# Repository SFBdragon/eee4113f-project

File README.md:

# EEE4113F Project - Antarctic Measurement System Communication Module

_Group 5_

---

TODO

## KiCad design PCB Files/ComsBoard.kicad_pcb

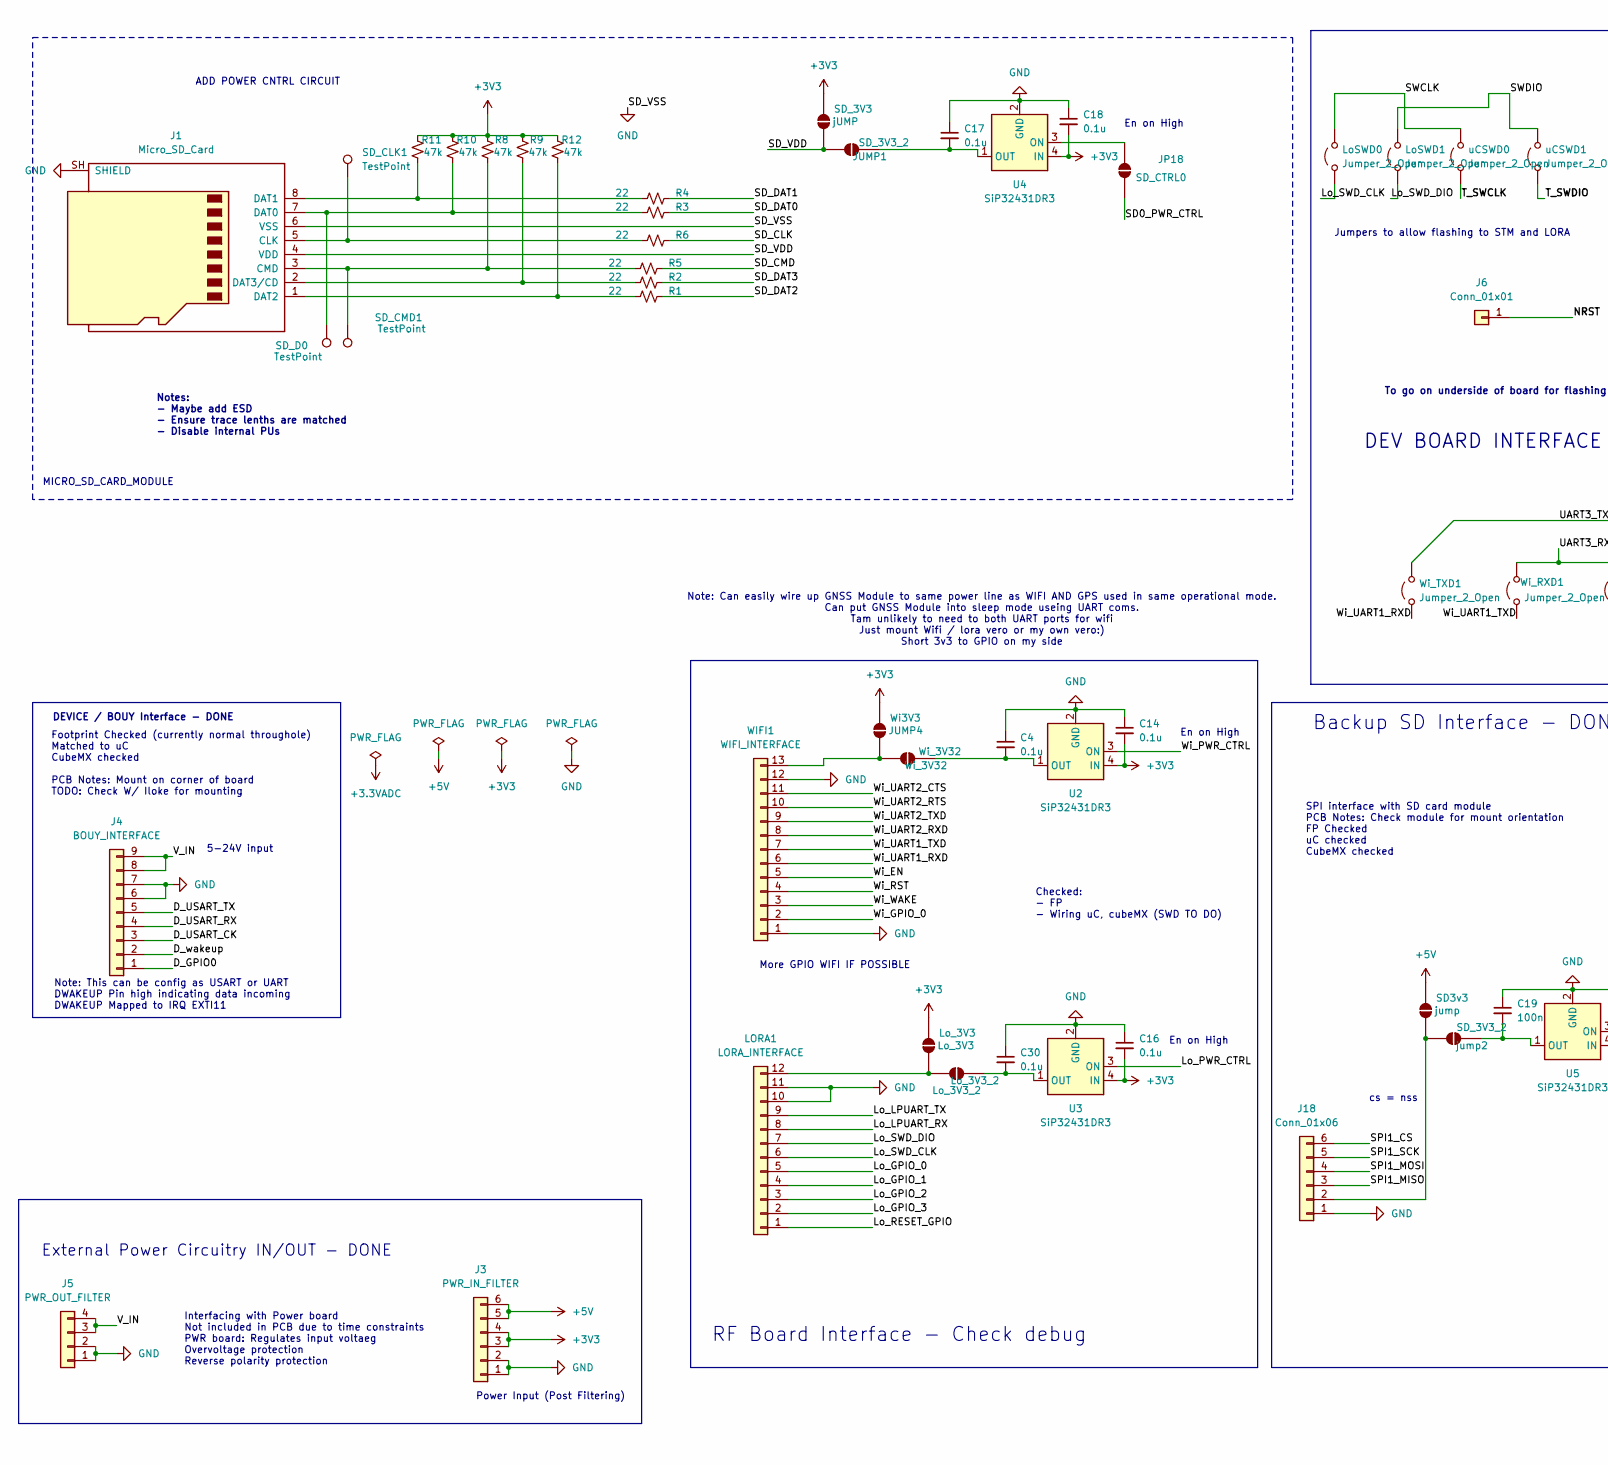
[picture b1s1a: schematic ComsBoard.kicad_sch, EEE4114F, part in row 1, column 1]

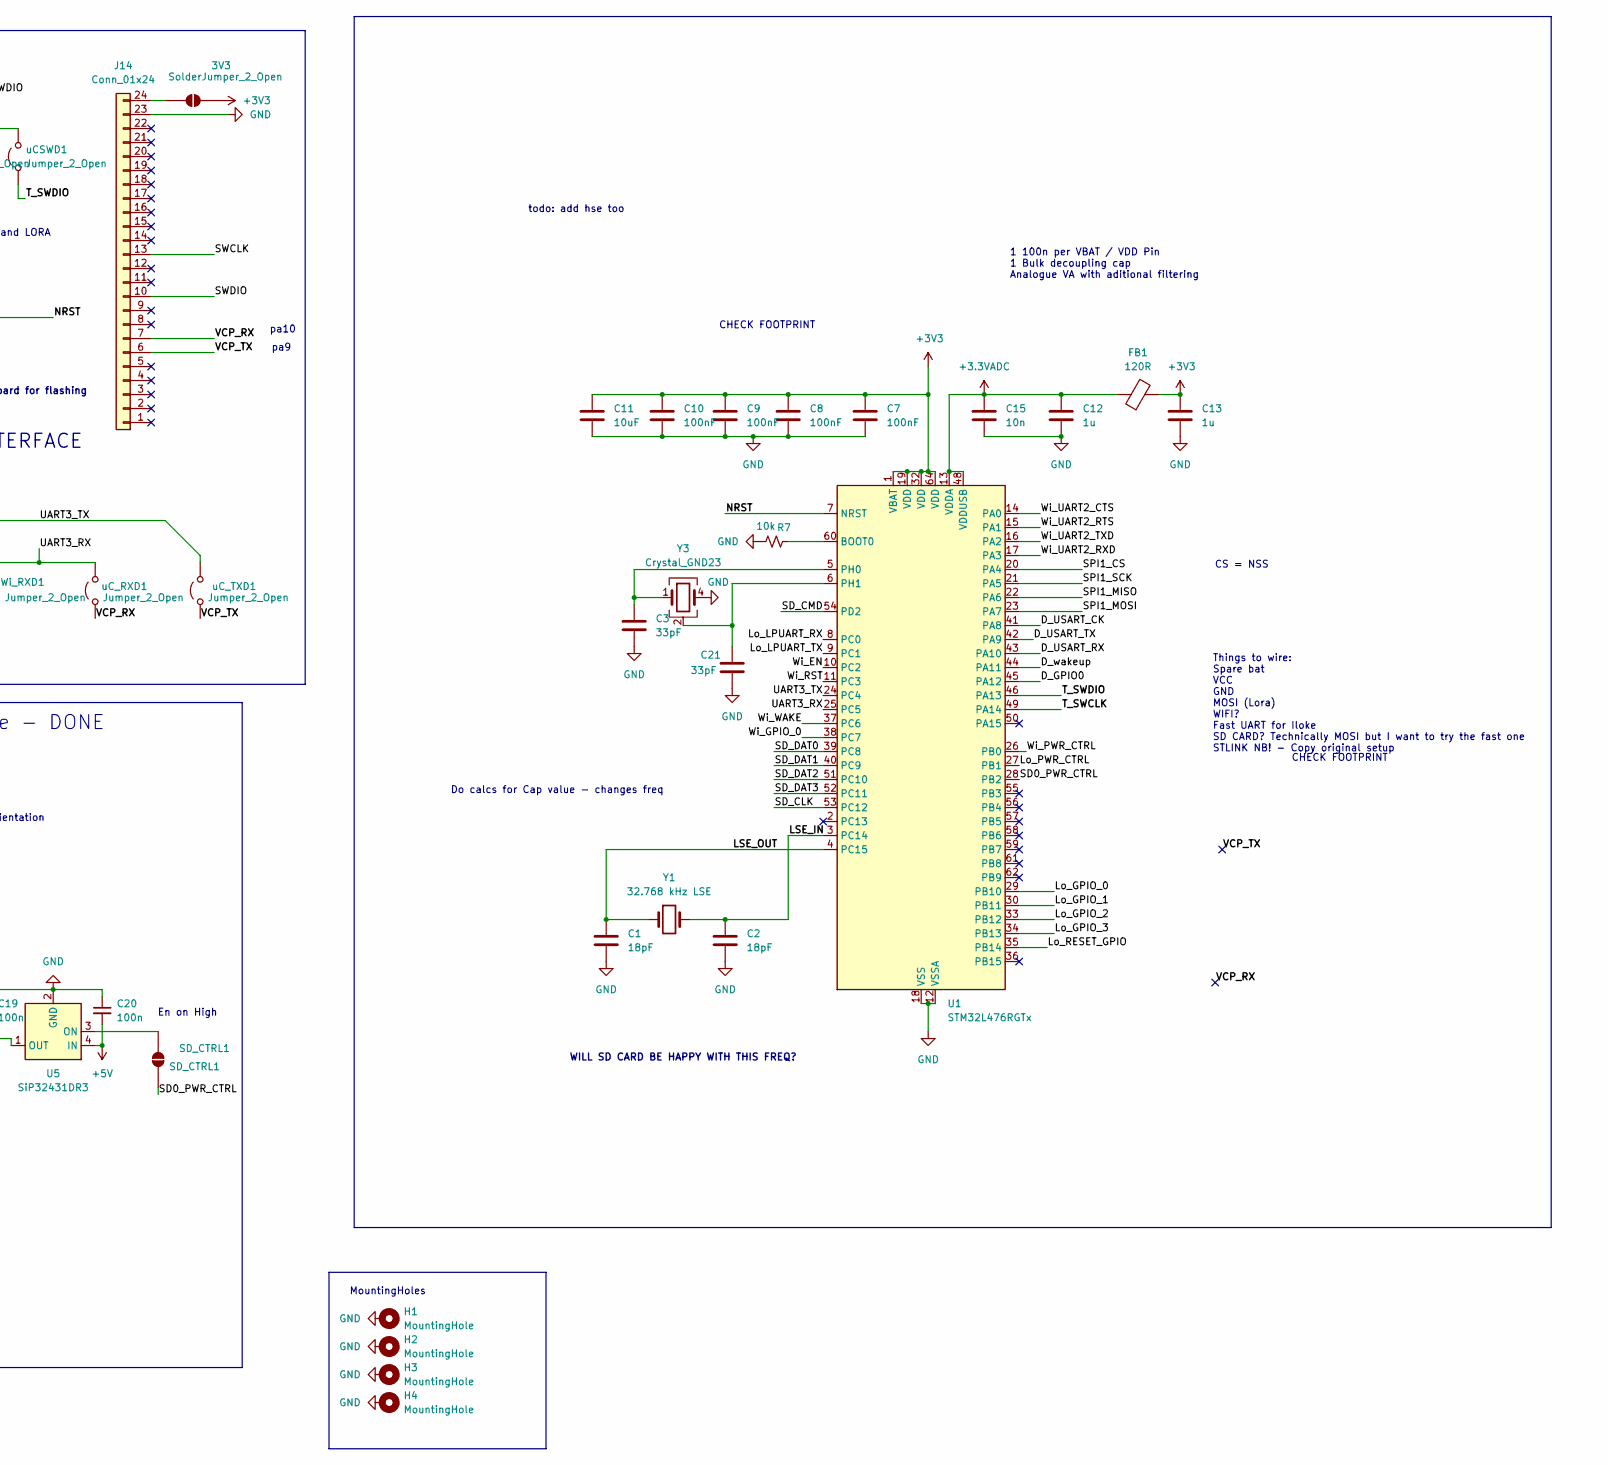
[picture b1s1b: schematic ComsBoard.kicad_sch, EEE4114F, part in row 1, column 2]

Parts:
3V3: SolderJumper_2_Open; SolderJumper-2_P1.3mm_Open_RoundedPad1.0x1.5mm
C1, C2: 18pF; C_0603_1608Metric
C3, C21: 33pF; C_0603_1608Metric
C4, C14, C16, C17, C18, C30: 0.1u; C_0603_1608Metric
C7, C8, C9, C10: 100nF; C_0603_1608Metric
C11: 10uF; C_0603_1608Metric
C12, C13: 1u; C_0603_1608Metric
C15: 10n; C_0603_1608Metric
C19, C20: 100n; C_0603_1608Metric
FB1: 120R; L_0603_1608Metric
H1, H2, H3, H4: MountingHole; MountingHole_3.2mm_M3_DIN965_Pad
J1: Micro_SD_Card; microSD_HC_Molex_47219-2001
J3: PWR_IN_FILTER; PinHeader_1x06_P2.54mm_Vertical
J4: BOUY_INTERFACE; PinHeader_1x09_P2.54mm_Vertical
J5: PWR_OUT_FILTER; PinHeader_1x04_P2.54mm_Vertical
J6: Conn_01x01; PinSocket_1x01_P2.54mm_Vertical
J14: Conn_01x24; PinSocket_1x24_P2.54mm_Vertical
J18: Conn_01x06; PinHeader_1x06_P2.54mm_Vertical
JP18: SD_CTRL0; SolderJumper-2_P1.3mm_Open_RoundedPad1.0x1.5mm
JUMP1: SD_3V3_2; SolderJumper-2_P1.3mm_Open_RoundedPad1.0x1.5mm
LORA1: LORA_INTERFACE; PinHeader_1x12_P2.54mm_Vertical
LoSWD0, LoSWD1: Jumper_2_Open; PinSocket_1x02_P2.54mm_Vertical
Lo_3V3: Lo_3V3; SolderJumper-2_P1.3mm_Open_RoundedPad1.0x1.5mm
Lo_3V3_2: Lo_3V3_2; SolderJumper-2_P1.3mm_Open_RoundedPad1.0x1.5mm
R1, R2, R3, R4, R5, R6: 22; R_0603_1608Metric
R7: 10k; R_0603_1608Metric
R8, R9, R10, R11, R12: 47k; R_0603_1608Metric
SD3v3: jump; SolderJumper-2_P1.3mm_Open_RoundedPad1.0x1.5mm
SD_3V3: jUMP; SolderJumper-2_P1.3mm_Open_RoundedPad1.0x1.5mm
SD_CLK1: TestPoint; TestPoint_Pad_D1.5mm
SD_CMD1: TestPoint; TestPoint_Pad_D1.5mm
SD_CTRL1: SD_CTRL1; SolderJumper-2_P1.3mm_Open_RoundedPad1.0x1.5mm
SD_D0: TestPoint; TestPoint_Pad_D1.5mm
U1: STM32L476RGTx; LQFP-64_10x10mm_P0.5mm
U2, U3, U4, U5: SiP32431DR3; SOT-363_SC-70-6
WIFI1: WIFI_INTERFACE; PinSocket_1x13_P2.54mm_Vertical
Wi3V3: JUMP4; SolderJumper-2_P1.3mm_Open_RoundedPad1.0x1.5mm
Wi_3V32: Wi_3V32; SolderJumper-2_P1.3mm_Open_RoundedPad1.0x1.5mm
Wi_RXD1: Jumper_2_Open; PinSocket_1x02_P2.54mm_Vertical
Wi_TXD1: Jumper_2_Open; PinSocket_1x02_P2.54mm_Vertical
Y1: 32.768 kHz LSE; Crystal_SMD_3215-2Pin_3.2x1.5mm
Y3: Crystal_GND23; Crystal_SMD_3225-4Pin_3.2x2.5mm
jump2: SD_3V3_2; SolderJumper-2_P1.3mm_Open_RoundedPad1.0x1.5mm
uCSWD0, uCSWD1: Jumper_2_Open; PinSocket_1x02_P2.54mm_Vertical
uC_RXD1: Jumper_2_Open; PinSocket_1x02_P2.54mm_Vertical
uC_TXD1: Jumper_2_Open; PinSocket_1x02_P2.54mm_Vertical

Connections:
+3.3VADC: C12.1, C15.1, FB1.1, U1.13 (VDDA), U1.48 (VDDUSB)
+5V: C20.2, J3.5, J3.6, SD3v3.2 (B), U5.4 (IN)
/D_GPIO0: J4.1, U1.45 (PA12)
/D_USART_CK: J4.3, U1.41 (PA8)
/D_USART_RX: J4.4, U1.43 (PA10)
/D_USART_TX: J4.5, U1.42 (PA9)
/D_wakeup: J4.2, U1.44 (PA11)
/LSE_IN: C2.1, U1.3 (PC14), Y1.2
/LSE_OUT: C1.1, U1.4 (PC15), Y1.1
/Lo_GPIO_0: LORA1.5, U1.29 (PB10)
/Lo_GPIO_1: LORA1.4, U1.30 (PB11)
/Lo_GPIO_2: LORA1.3, U1.33 (PB12)
/Lo_GPIO_3: LORA1.2, U1.34 (PB13)
/Lo_LPUART_RX: LORA1.8, U1.8 (PC0)
/Lo_LPUART_TX: LORA1.9, U1.9 (PC1)
/Lo_PWR_CTRL: U1.27 (PB1), U3.3 (ON)
/Lo_RESET_GPIO: LORA1.1, U1.35 (PB14)
/Lo_SWD_CLK: LORA1.6, LoSWD0.1 (A)
/Lo_SWD_DIO: LORA1.7, LoSWD1.1 (A)
/NRST: J6.1 (Pin_1_1), U1.7 (NRST)
/SD0_PWR_CTRL: JP18.2 (B), SD_CTRL1.2 (B), U1.28 (PB2)
/SD_CLK: R6.2, U1.53 (PC12)
/SD_CMD: R5.2, U1.54 (PD2)
/SD_DAT0: R3.2, U1.39 (PC8)
/SD_DAT1: R4.2, U1.40 (PC9)
/SD_DAT2: R1.2, U1.51 (PC10)
/SD_DAT3: R2.2, U1.52 (PC11)
/SPI1_CS: J18.6, U1.20 (PA4)
/SPI1_MISO: J18.3, U1.22 (PA6)
/SPI1_MOSI: J18.4, U1.23 (PA7)
/SPI1_SCK: J18.5, U1.21 (PA5)
/SWCLK: J14.13, LoSWD0.2 (B), uCSWD0.2 (B)
/SWDIO: J14.10, LoSWD1.2 (B), uCSWD1.2 (B)
/T_SWCLK: U1.49 (PA14), uCSWD0.1 (A)
/T_SWDIO: U1.46 (PA13), uCSWD1.1 (A)
/UART3_RX: U1.25 (PC5), Wi_RXD1.2 (B), uC_RXD1.2 (B)
/UART3_TX: U1.24 (PC4), Wi_TXD1.2 (B), uC_TXD1.2 (B)
/VCP_RX: J14.7, uC_RXD1.1 (A)
/VCP_TX: J14.6, uC_TXD1.1 (A)
/V_IN: J4.8, J4.9, J5.3, J5.4
/Wi_EN: U1.10 (PC2), WIFI1.5
/Wi_GPIO_0: U1.38 (PC7), WIFI1.2
/Wi_PWR_CTRL: U1.26 (PB0), U2.3 (ON)
/Wi_RST: U1.11 (PC3), WIFI1.4
/Wi_UART1_RXD: WIFI1.6, Wi_TXD1.1 (A)
/Wi_UART1_TXD: WIFI1.7, Wi_RXD1.1 (A)
/Wi_UART2_CTS: U1.14 (PA0), WIFI1.11
/Wi_UART2_RTS: U1.15 (PA1), WIFI1.10
/Wi_UART2_RXD: U1.17 (PA3), WIFI1.8
/Wi_UART2_TXD: U1.16 (PA2), WIFI1.9
/Wi_WAKE: U1.37 (PC6), WIFI1.3
GND: C1.2, C2.2, C3.2, C4.1, C7.2, C8.2, C9.2, C10.2, C11.2, C12.2, C13.2, C14.1, C15.2, C16.1, C17.1, C18.1, C19.1, C20.1, C21.2, C30.1, J1.6 (VSS), J1.SH (SHIELD), J3.1, J3.2, J4.6, J4.7, J5.1, J5.2, J14.23, J18.1, LORA1.10, LORA1.11, R7.1, U1.12 (VSSA), U1.18 (VSS), U1.31 (VSS), U1.47 (VSS), U1.63 (VSS), U2.2 (GND), U2.5 (GND), U3.2 (GND), U3.5 (GND), U4.2 (GND), U4.5 (GND), U5.2 (GND), U5.5 (GND), WIFI1.1, WIFI1.12, Y3.4; also elsewhere on the board
unnamed: 3V3.1 (A), J14.24
unnamed: J1.5 (CLK), R6.1, SD_CLK1.1 (1_1)
unnamed: J1.3 (CMD), R5.1, R8.1, SD_CMD1.1 (1_1)
unnamed: J1.7 (DAT0), R3.1, R10.1, SD_D0.1 (1_1)
unnamed: J1.8 (DAT1), R4.1, R11.1
unnamed: J1.1 (DAT2), R1.1, R12.1
unnamed: J1.2 (DAT3/CD), R2.1, R9.1
unnamed: J18.2, SD3v3.1 (A), jump2.2 (B)
unnamed: JP18.1 (A), U4.3 (ON)
unnamed: C17.2, JUMP1.1 (A), U4.1 (OUT)
unnamed: LORA1.12, Lo_3V3.1 (A), Lo_3V3_2.2 (B)
unnamed: C30.2, Lo_3V3_2.1 (A), U3.1 (OUT)
unnamed: SD_CTRL1.1 (A), U5.3 (ON)
unnamed: R7.2, U1.60 (BOOT0)
unnamed: C3.1, U1.5 (PH0), Y3.1
unnamed: C21.1, U1.6 (PH1), Y3.2 (G), Y3.3 (G)
unnamed: C4.2, U2.1 (OUT), Wi_3V32.1 (A)
unnamed: C19.2, U5.1 (OUT), jump2.1 (A)
unnamed: WIFI1.13, Wi3V3.1 (A), Wi_3V32.2 (B)

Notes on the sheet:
Note: Can easily wire up GNSS Module to same power line as WIFI AND GPS used in same operational mode. Can put GNSS Module into sleep mode useing UART coms. Tam unlikely to need to both UART ports for wifi Just mount Wifi / lora vero or my own vero:) Short 3v3 to GPIO on my side
More GPIO WIFI IF POSSIBLE
CHECK FOOTPRINT
cs = nss
SPI interface with SD card module PCB Notes: Check module for mount orientation FP Checked uC checked CubeMX checked
Footprint Checked (currently normal throughole) Matched to uC CubeMX checked PCB Notes: Mount on corner of board TODO: Check W/ Iloke for mounting
En on High
RF Board Interface - Check debug
Note: This can be config as USART or UART DWAKEUP Pin high indicating data incoming DWAKEUP Mapped to IRQ EXTI11
Things to wire: Spare bat VCC GND MOSI (Lora) WIFI? Fast UART for Iloke SD CARD? Technically MOSI but I want to try the fast one STLINK NB! - Copy original setup
DEVICE / BOUY Interface - DONE
WILL SD CARD BE HAPPY WITH THIS FREQ?
pa9
Power Input (Post Filtering)
CS = NSS
Interfacing with Power board Not included in PCB due to time constraints PWR board: Regulates input voltaeg Overvoltage protection Reverse polarity protection
External Power Circuitry IN/OUT - DONE
Notes: - Maybe add ESD - Ensure trace lenths are matched - Disable internal PUs
todo: add hse too
To go on underside of board for flashing
Jumpers to allow flashing to STM and LORA
pa10
Checked: - FP - Wiring uC, cubeMX (SWD TO DO)
Backup SD Interface - DONE
DEV BOARD INTERFACE
ADD POWER CNTRL CIRCUIT
MICRO_SD_CARD_MODULE
1 100n per VBAT / VDD Pin 1 Bulk decoupling cap Analogue VA with aditional filtering
5-24V input
MountingHoles
Do calcs for Cap value - changes freq

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
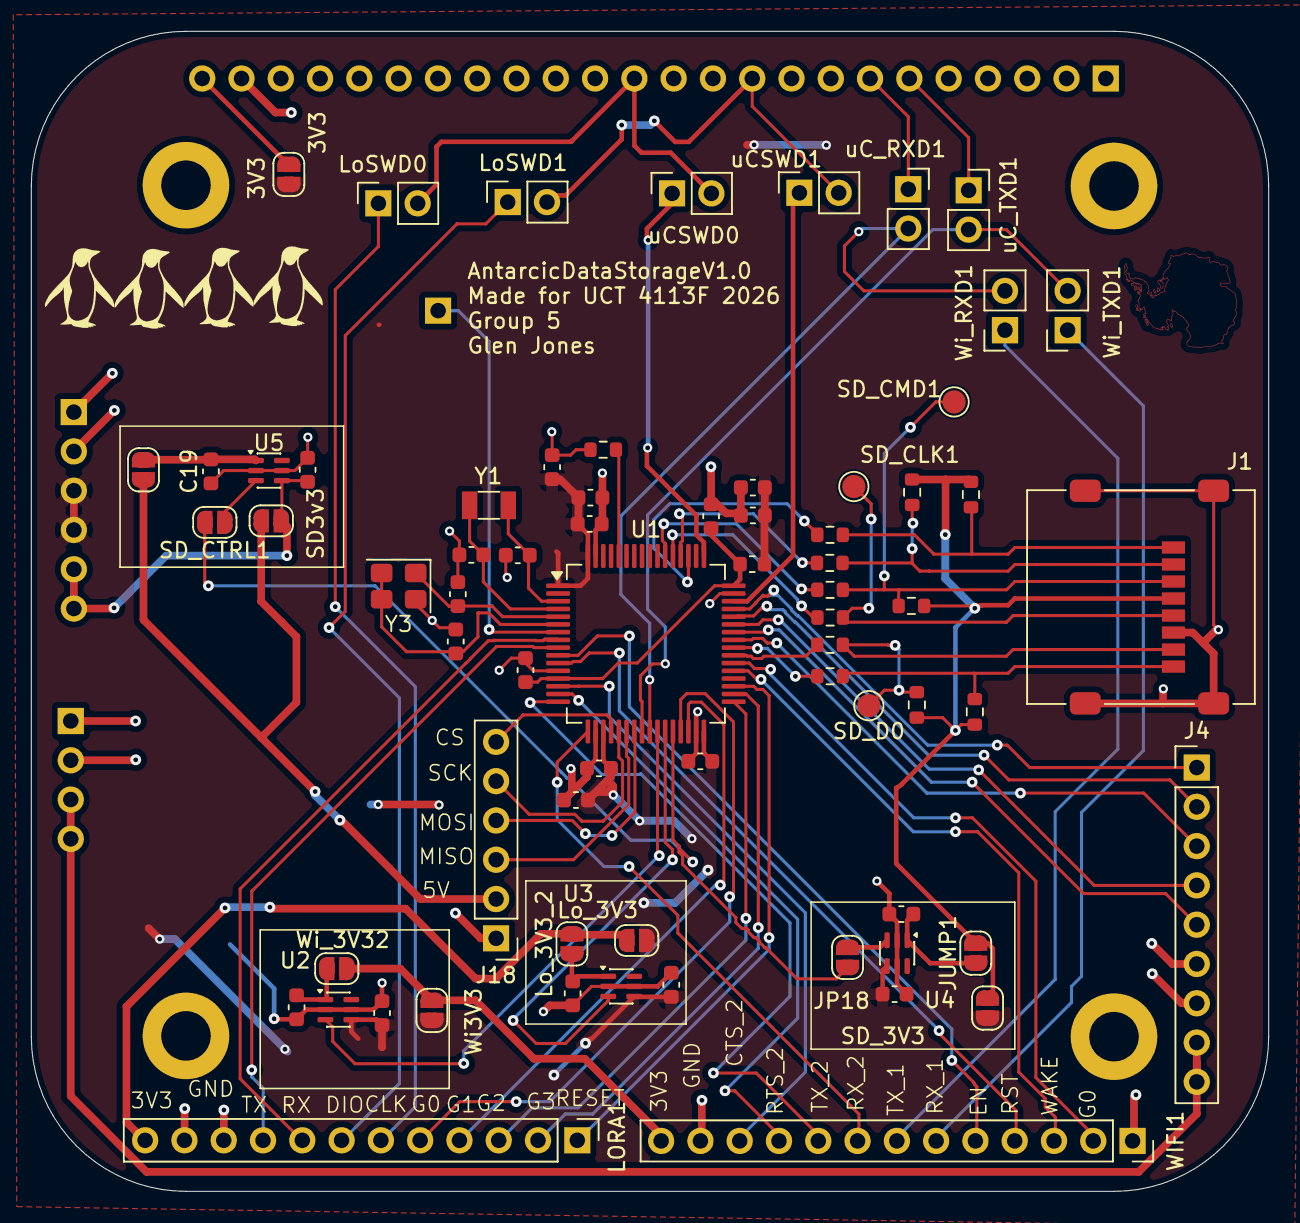
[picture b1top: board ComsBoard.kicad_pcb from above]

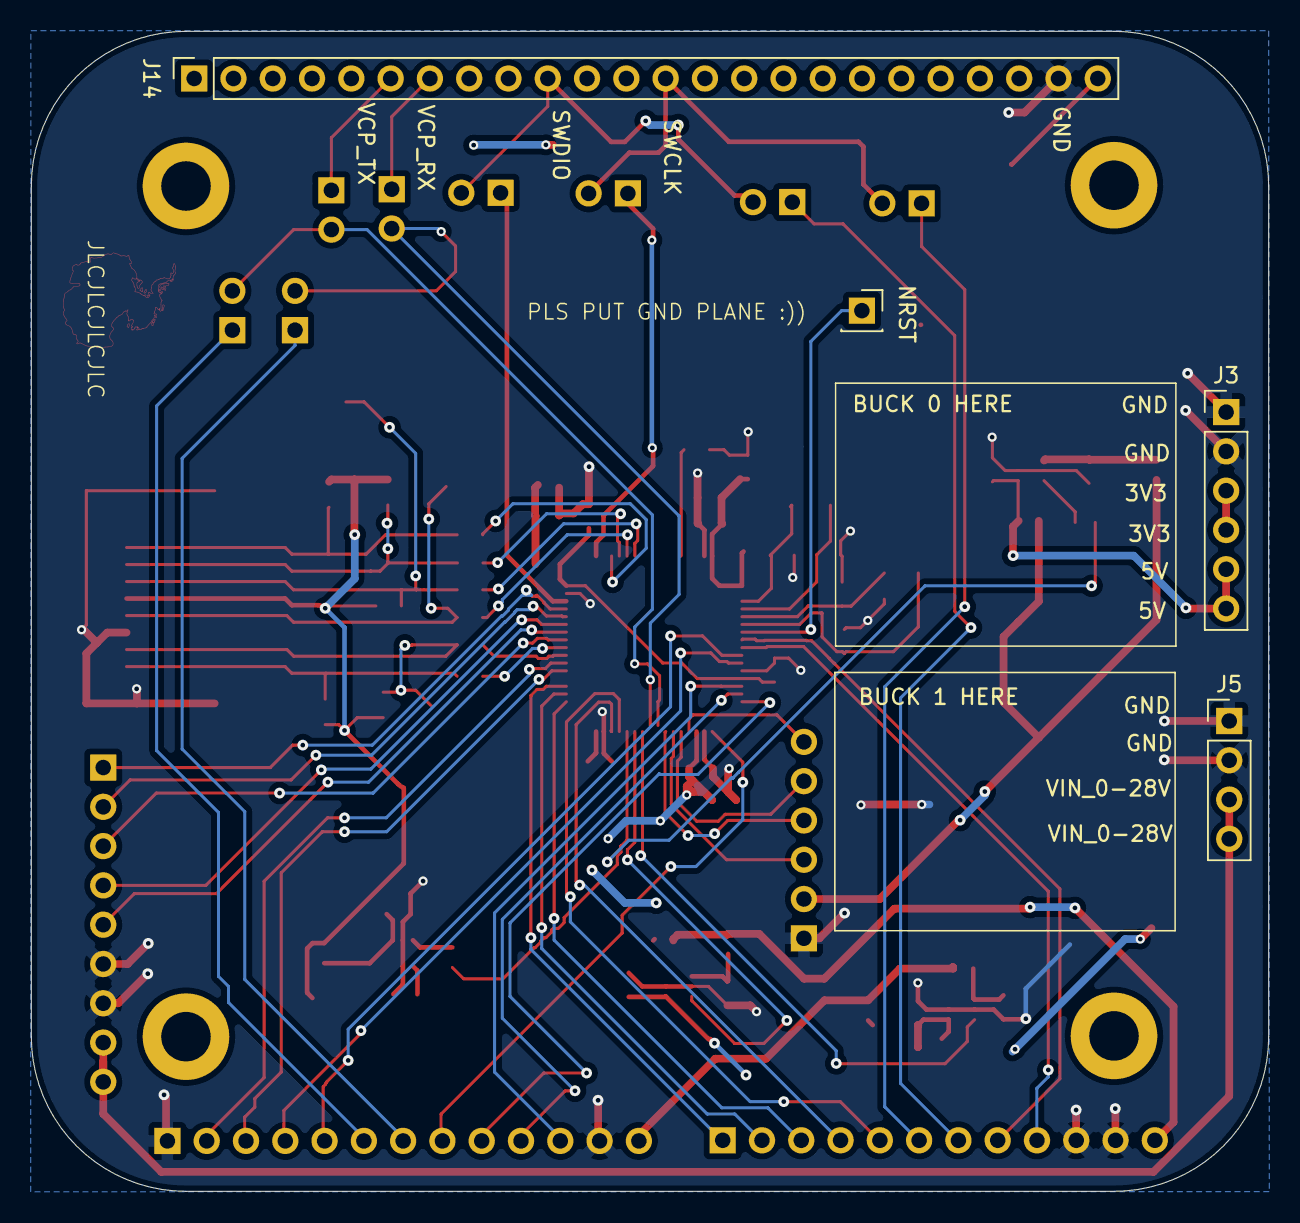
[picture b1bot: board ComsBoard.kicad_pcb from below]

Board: 2 copper layers, 80.0 x 75.0 mm, 77 parts (4 on the bottom side), 73 nets.

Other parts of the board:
C1#2: 1uF; C_0603_1608Metric
C6: 100nF; C_0603_1608Metric

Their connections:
GND: C1#2.2, C6.2; also elsewhere on the board

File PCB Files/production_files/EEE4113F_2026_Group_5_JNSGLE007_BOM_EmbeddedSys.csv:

Comment,Designator,Footprint,LCSC,Quantity
0.1u,"C14,C16,C17,C18,C30,C4",C_0603_1608Metric,C14663,6
100n,"C19,C20",C_0603_1608Metric,C14663,2
100nF,"C10,C6,C7,C8,C9",C_0603_1608Metric,C14663,5
10k,R7,R_0603_1608Metric,C25804,1
10n,C15,C_0603_1608Metric,C57112,1
10uF,C11,C_0603_1608Metric,C19702,1
120R,FB1,L_0603_1608Metric,C1002,1
18pF,C2,C_0603_1608Metric,C1647,1
1u,"C12,C13",C_0603_1608Metric,C15849,2
1uF,C1,C_0603_1608Metric,C15849,1
22,"R1,R2,R3,R4,R5,R6",R_0603_1608Metric,C23345,6
32.768 kHz LSE,Y1,Crystal_SMD_3215-2Pin_3.2x1.5mm,C32346,1
33pF,"C21,C3",C_0603_1608Metric,C1663,2
47k,"R10,R11,R12,R8,R9",R_0603_1608Metric,C25819,5
Crystal_GND23,Y3,Crystal_SMD_3225-4Pin_3.2x2.5mm,C9002,1
Micro_SD_Card,J1,microSD_HC_Molex_47219-2001,C164170,1
STM32L476RGTx,U1,LQFP-64_10x10mm_P0.5mm,C74797,1
SiP32431DR3,"U2,U3,U4,U5",SOT-363_SC-70-6,C141606,4

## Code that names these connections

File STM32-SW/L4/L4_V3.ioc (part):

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Mcu.Name=STM32L476R(C-E-G)Tx
Mcu.Package=LQFP64
Mcu.UserName=STM32L476RGTx
PA10.GPIOParameters=GPIO_Label
PA10.GPIO_Label=D_USART_RX
PA10.Mode=Asynchronous
PA10.Signal=USART1_RX
PA11.GPIOParameters=GPIO_Label
PA11.GPIO_Label=D_WAKE
PA11.Signal=GPXTI11
PA12.GPIOParameters=GPIO_Label
PA12.GPIO_Label=D_GPIO0
PA12.Signal=GPIO_Input
PA13\ (JTMS-SWDIO).Mode=Serial_Wire
PA13\ (JTMS-SWDIO).Signal=SYS_JTMS-SWDIO
PA14\ (JTCK-SWCLK).Mode=Serial_Wire
PA14\ (JTCK-SWCLK).Signal=SYS_JTCK-SWCLK
PA2.GPIOParameters=GPIO_Label
PA2.GPIO_Label=Wi_USART2_TX
PA2.Mode=Asynchronous
PA2.Signal=USART2_TX
PA3.GPIOParameters=GPIO_Label
PA3.GPIO_Label=Wi_USART2_RX
PA3.Mode=Asynchronous
PA3.Signal=USART2_RX
PA4.GPIOParameters=GPIO_PuPd,GPIO_Label
PA4.GPIO_Label=SD_GPIO_INPUT
PA4.GPIO_PuPd=GPIO_PULLDOWN
PA4.Signal=GPIO_Input
PA5.GPIOParameters=GPIO_Label
PA5.GPIO_Label=SD_SPI1_SCK
PA5.Mode=Full_Duplex_Master
PA5.Signal=SPI1_SCK
PA6.GPIOParameters=GPIO_Label
PA6.GPIO_Label=SD_SPI1_MISO
PA6.Mode=Full_Duplex_Master
PA6.Signal=SPI1_MISO
PA7.GPIOParameters=GPIO_Label
PA7.GPIO_Label=SD_SPI1_MOSI
PA7.Mode=Full_Duplex_Master
PA7.Signal=SPI1_MOSI
PA9.GPIOParameters=GPIO_Label
PA9.GPIO_Label=D_USART_TX
PA9.Mode=Asynchronous
PA9.Signal=USART1_TX
PB0.GPIOParameters=GPIO_Label
PB0.GPIO_Label=Wi_PWR_CTRL
PB0.Signal=GPIO_Output
PB1.GPIOParameters=GPIO_Label
PB1.GPIO_Label=Lo_PWR_CTRL
PB1.Signal=GPIO_Output
PB10.GPIOParameters=GPIO_Label
PB10.GPIO_Label=Lo_GPIO_0
PB10.Signal=GPIO_Output
PB11.GPIOParameters=GPIO_Label
PB11.GPIO_Label=Lo_GPIO_1
PB11.Signal=GPIO_Output
PB12.GPIOParameters=GPIO_Label
PB12.GPIO_Label=Lo_GPIO_2
PB12.Signal=GPIO_Output
PB13.Mode=I2C
PB13.Signal=I2C2_SCL
PB14.Mode=I2C
PB14.Signal=I2C2_SDA
PB2.GPIOParameters=GPIO_Label
PB2.GPIO_Label=SD0_PWR_CTRL
PB2.Signal=GPIO_Output
PC0.GPIOParameters=GPIO_Label
PC0.GPIO_Label=L0_LPUART1_RX
PC0.Mode=Asynchronous
PC0.Signal=LPUART1_RX
PC1.GPIOParameters=GPIO_Label
PC1.GPIO_Label=L0_LPUART1_TX
PC1.Mode=Asynchronous
PC1.Signal=LPUART1_TX
PC10.Mode=SD_4_bits_Wide_bus
PC10.Signal=SDMMC1_D2
PC11.Mode=SD_4_bits_Wide_bus
PC11.Signal=SDMMC1_D3
PC12.GPIOParameters=GPIO_PuPd,GPIO_Speed_High_Default,GPIO_Mode
PC12.GPIO_Mode=GPIO_MODE_AF_PP
PC12.GPIO_PuPd=GPIO_NOPULL
PC12.GPIO_Speed_High_Default=GPIO_SPEED_FREQ_VERY_HIGH
PC12.Mode=SD_4_bits_Wide_bus
PC12.Signal=SDMMC1_CK
PC2.GPIOParameters=GPIO_Label
PC2.GPIO_Label=Wi_EN
PC2.Signal=GPIO_Output
PC3.GPIOParameters=GPIO_Label
PC3.GPIO_Label=Wi_RST
PC3.Signal=GPIO_Output
PC4.GPIOParameters=GPIO_Label
PC4.GPIO_Label=Wi_USART3_TX
PC4.Mode=Asynchronous
PC4.Signal=USART3_TX
PC5.GPIOParameters=GPIO_Label
PC5.GPIO_Label=Wi_USART3_RX
PC5.Mode=Asynchronous
PC5.Signal=USART3_RX
PC6.GPIOParameters=GPIO_Label
PC6.GPIO_Label=Wi_WAKE
PC6.Signal=GPIO_Output
PC7.GPIOParameters=GPIO_Label
PC7.GPIO_Label=Wi_GPIO_0
PC7.Signal=GPIO_Output
PC8.GPIOParameters=GPIO_PuPd,GPIO_Speed_High_Default,GPIO_Mode
PC8.GPIO_Mode=GPIO_MODE_AF_PP
PC8.GPIO_PuPd=GPIO_NOPULL
PC8.GPIO_Speed_High_Default=GPIO_SPEED_FREQ_VERY_HIGH
PC8.Mode=SD_4_bits_Wide_bus
PC8.Signal=SDMMC1_D0
PC9.Mode=SD_4_bits_Wide_bus
PC9.Signal=SDMMC1_D1
PD2.GPIOParameters=GPIO_PuPd,GPIO_Speed_High_Default,GPIO_Mode
PD2.GPIO_Mode=GPIO_MODE_AF_PP
PD2.GPIO_PuPd=GPIO_NOPULL
PD2.GPIO_Speed_High_Default=GPIO_SPEED_FREQ_VERY_HIGH
PD2.Mode=SD_4_bits_Wide_bus
PD2.Signal=SDMMC1_CMD
RCC.HSE_VALUE=12000000
RCC.SYSCLKFreq_VALUE=80000000
RCC.SYSCLKSource=RCC_SYSCLKSOURCE_PLLCLK
board=custom

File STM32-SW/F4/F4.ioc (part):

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Mcu.Name=STM32F446R(C-E)Tx
Mcu.Package=LQFP64
Mcu.UserName=STM32F446RCTx
PA0-WKUP.Mode=CTS_RTS
PA0-WKUP.Signal=USART2_CTS
PA1.Mode=CTS_RTS
PA1.Signal=USART2_RTS
PA10.GPIOParameters=GPIO_Label
PA10.GPIO_Label=D_USART1_RX
PA10.Mode=Synchronous
PA10.Signal=USART1_RX
PA11.GPIOParameters=GPIO_Label
PA11.GPIO_Label=D_wakeup
PA11.Signal=GPXTI11
PA13.Mode=Serial_Wire
PA13.Signal=SYS_JTMS-SWDIO
PA14.Mode=Serial_Wire
PA14.Signal=SYS_JTCK-SWCLK
PA15.GPIOParameters=GPIO_Label
PA15.GPIO_Label=SD_SPI1_NSS
PA15.Mode=NSS_Signal_Hard_Output
PA15.Signal=SPI1_NSS
PA2.Mode=Asynchronous
PA2.Signal=USART2_TX
PA3.Mode=Asynchronous
PA3.Signal=USART2_RX
PA5.GPIOParameters=GPIO_Label
PA5.GPIO_Label=SD_SPI1_SCK
PA5.Mode=Full_Duplex_Master
PA5.Signal=SPI1_SCK
PA6.GPIOParameters=GPIO_Label
PA6.GPIO_Label=SD_SPI1_MISO
PA6.Mode=Full_Duplex_Master
PA6.Signal=SPI1_MISO
PA7.GPIOParameters=GPIO_Label
PA7.GPIO_Label=SD_SPI1_MOSI
PA7.Mode=Full_Duplex_Master
PA7.Signal=SPI1_MOSI
PA8.GPIOParameters=GPIO_Label
PA8.GPIO_Label=D_USART1_CK
PA8.Mode=Synchronous
PA8.Signal=USART1_CK
PA9.GPIOParameters=GPIO_Label
PA9.GPIO_Label=D_USART_TX
PA9.Mode=Synchronous
PA9.Signal=USART1_TX
PB4.GPIOParameters=GPIO_Label
PB4.GPIO_Label=LED_4
PB4.Signal=GPIO_Output
PB5.GPIOParameters=GPIO_Label
PB5.GPIO_Label=LED_3
PB5.Signal=GPIO_Output
PB6.GPIOParameters=GPIO_Label
PB6.GPIO_Label=LED_2
PB6.Signal=GPIO_Output
PB7.GPIOParameters=GPIO_Label
PB7.GPIO_Label=LED_1
PB7.Signal=GPIO_Output
PB8.GPIOParameters=GPIO_Label
PB8.GPIO_Label=OLED_SCL
PB8.Mode=I2C
PB8.Signal=I2C1_SCL
PB9.GPIOParameters=GPIO_Label
PB9.GPIO_Label=OLED_SDA
PB9.Mode=I2C
PB9.Signal=I2C1_SDA
PH0-OSC_IN.Mode=HSE-External-Oscillator
PH0-OSC_IN.Signal=RCC_OSC_IN
PH1-OSC_OUT.Mode=HSE-External-Oscillator
PH1-OSC_OUT.Signal=RCC_OSC_OUT
board=custom

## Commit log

2026-04-08 REAMDE.md: fix spelling
2026-04-09 control-panel: started GUI implementation with Slint
2026-04-11 laptop drivers: define interface and Rust integration
2026-04-15 specify LoRa CRC bytes
2026-04-17 Added F4 SW Setup (incl OLED libs)
2026-04-22 add mac addresses to laptop nic driver interface
2026-04-23 headers: settle inter-subsystem interface definitions for the time being
2026-05-05 Inital L4 Flash and GPIO Test
2026-05-05 12MHz Crystal HSE Out test
2026-05-05 Added I2C OLED for debugging
2026-05-05 SDMMC no longer crashing code
2026-05-05 successful non-fail SDMMC init
2026-05-06 lot's of protocol work
2026-05-06 move headers to L4 project
2026-05-07 Fixed wack SDMMC and OLED bug
2026-05-07 Flipping into 4-bit mode
2026-05-07 FATFS Testing Read / write
2026-05-10 gui: lots of progress, looks ugly though
2026-05-11 gui: data storage and display
2026-05-11 added serial output helper func
2026-05-11 Device interrupt Toggle
2026-05-11 SDMMC Debugging
2026-05-11 Fixed Hardware level SDMMC
2026-05-11 SDMCC Test write surviving power cycles
2026-05-12 Fixes RTC and GPIO wake from STOP
2026-05-12 Basic DMA working
2026-05-12 fixed DMA -> SD -> READ SD
2026-05-12 Fixed STOP SDMMC clash
2026-05-12 LPUART WORKING
2026-05-12 Lora RX TX done
2026-05-12 WIFI RX, TX WORKING
2026-05-13 for glen
2026-05-13 pushing for shaun
2026-05-13 for glen 2
2026-05-13 stop deleting my shit
2026-05-13 glen wont gib gps :(
2026-05-13 LoRa ATP test code - no payload available
2026-05-13 BLOCKED DATA, NO SIZE SEP
2026-05-13 changes to test_lora.c
2026-05-14 wifi test code
2026-05-14 minor atp02 updates
2026-05-14 atp02 test results files
2026-05-14 buoy side atp02 test results
2026-05-15 Pre-test
2026-05-15 integration testing: implement mock-module, UdpMockRadios, fix protocol.c
2026-05-17 atps: testing, fixes, improvements, add Actions for builds
2026-05-17 actions: fix paths
2026-05-17 actions: add system dependencies
2026-05-17 integration: build Tamryn's code properly
2026-05-17 temporarily avoid linking rf subsystem
2026-05-18 atp test CLI feature, launch error improvements
2026-05-18 committing Enclosure Subsystem Files
2026-05-19 Pre-fixing quick lora recieve
2026-05-19 Post testing templates
2026-05-20 link rust lib
2026-05-20 fix lora send/recv len for esp-now
2026-05-20 new SHRC BY
2026-05-20 rename protocol.c
2026-05-20 Fixed reconfigurble LoRa window
2026-05-20 Active mode timeout
2026-05-20 Lora recieve working
2026-05-20 please work
2026-05-20 debug lora
2026-05-20 debug lora 2
2026-05-20 better crc
2026-05-20 best crc
2026-05-21 too tried for sd;lfjgno
2026-05-21 fixing stash
2026-05-21 uiowhdfosadhf
2026-05-21 Interfacing lowk cooking
2026-05-21 i don't remember
2026-05-21 buoy: disable crc
2026-05-21 incremental commit
2026-05-21 moved some things around and finally got interfaceable wifi firmware
2026-05-21 mac merge issues
2026-05-21 Rust wifi serial drivers
2026-05-21 Mid lecture
2026-05-21 complex and simple 'lora' firmware
2026-05-21 added PCB files
2026-05-22 final pre-demo tweaks
